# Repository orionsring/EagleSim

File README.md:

# AutoDesk EagleSim
This circuit is a completed senior design project with no patent.
This circuit is to build an Electronic Power Meter. Used to measure power consumpion on electronic devices. Practically a DYI. Do It Yourself! More files with written assembly instructions to come.

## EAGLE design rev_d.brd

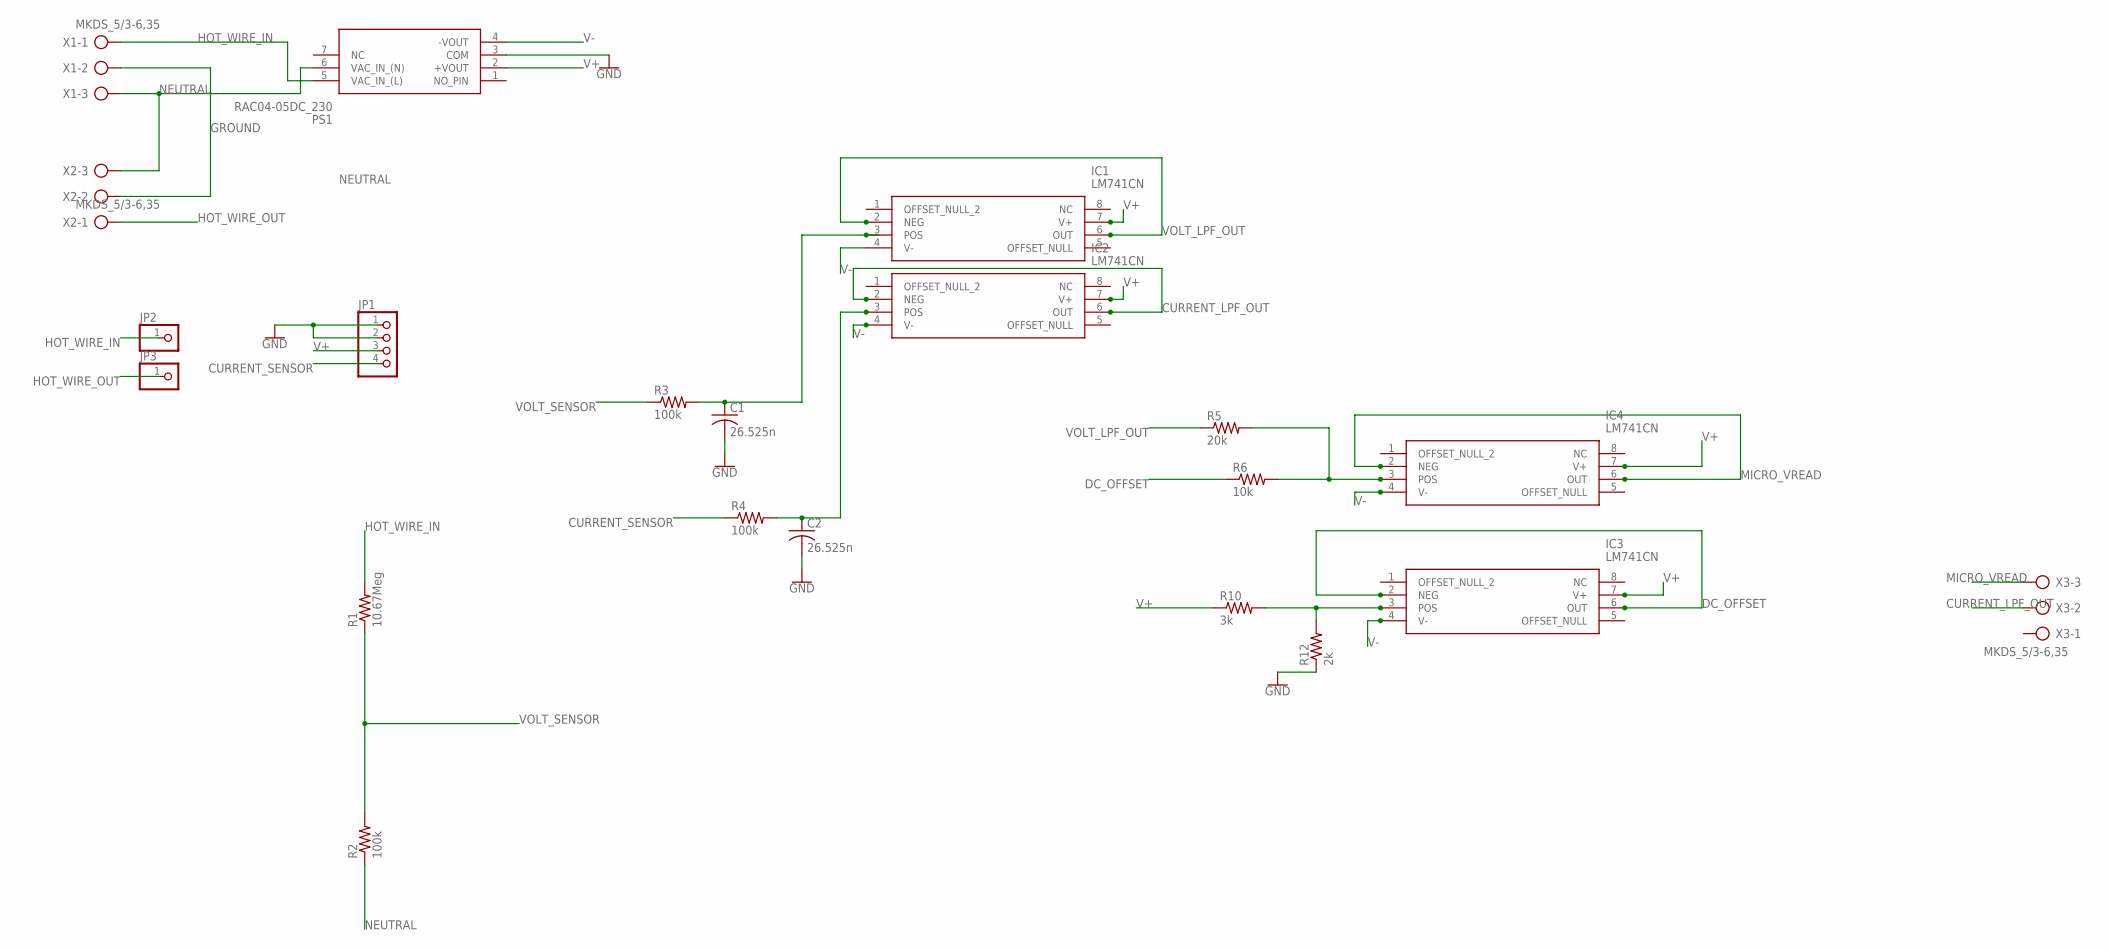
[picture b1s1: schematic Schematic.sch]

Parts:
C1, C2: 26.525n; C025-040X050; MPN MC0805B224K500A5.08MM
IC1, IC2, IC3, IC4: LM741CN; DIP254P762X508-8
JP1: PINHD-1X4; 1X04
JP2, JP3: PINHD-1X1; 1X01
PS1: RAC04-05DC_230; RAC04-0512DC230
R1: 10.67Meg; 0617/22
R2: 100k; 0617/22; MPN MFR3-100KFC
R3, R4: 100k; 0617/22; MPN MFR3-1K0FC
R5: 20k; 0617/22; MPN MFR4-20KFI
R6: 10k; 0617/22; MPN CCF5510K0FKE36
R10: 3k; 0617/22; MPN MFR4 3K3 1%
R12: 2k; 0617/22; MPN MFR4-2K0FI
X1, X2, X3: MKDS_5/3-6,35; MKDS_5/3-635

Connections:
CURRENT_LPF_OUT: IC2.2 (NEG), IC2.6 (OUT), X3.2
CURRENT_SENSOR: JP1.4, R4.1
DC_OFFSET: IC3.2 (NEG), IC3.6 (OUT), R6.1
GND: C1.2, C2.2, JP1.1, JP1.2, PS1.3 (COM), R12.1
GROUND: X1.2, X2.2
HOT_WIRE_IN: JP2.1, PS1.5 (VAC_IN_(L)), R1.2, X1.1
HOT_WIRE_OUT: JP3.1, X2.1
MICRO_VREAD: IC4.2 (NEG), IC4.6 (OUT), X3.3
unnamed: C1.1, IC1.3 (POS), R3.2
unnamed: C2.1, IC2.3 (POS), R4.2
unnamed: IC4.3 (POS), R5.2, R6.2
unnamed: IC3.3 (POS), R10.2, R12.2
NEUTRAL: PS1.6 (VAC_IN_(N)), R2.1, X1.3, X2.3
V+: IC1.7 (V+), IC2.7 (V+), IC3.7 (V+), IC4.7 (V+), JP1.3, PS1.2 (+VOUT), R10.1
V-: IC1.4 (V-), IC2.4 (V-), IC3.4 (V-), IC4.4 (V-), PS1.4 (-VOUT)
VOLT_LPF_OUT: IC1.2 (NEG), IC1.6 (OUT), R5.1
VOLT_SENSOR: R1.1, R2.2, R3.1

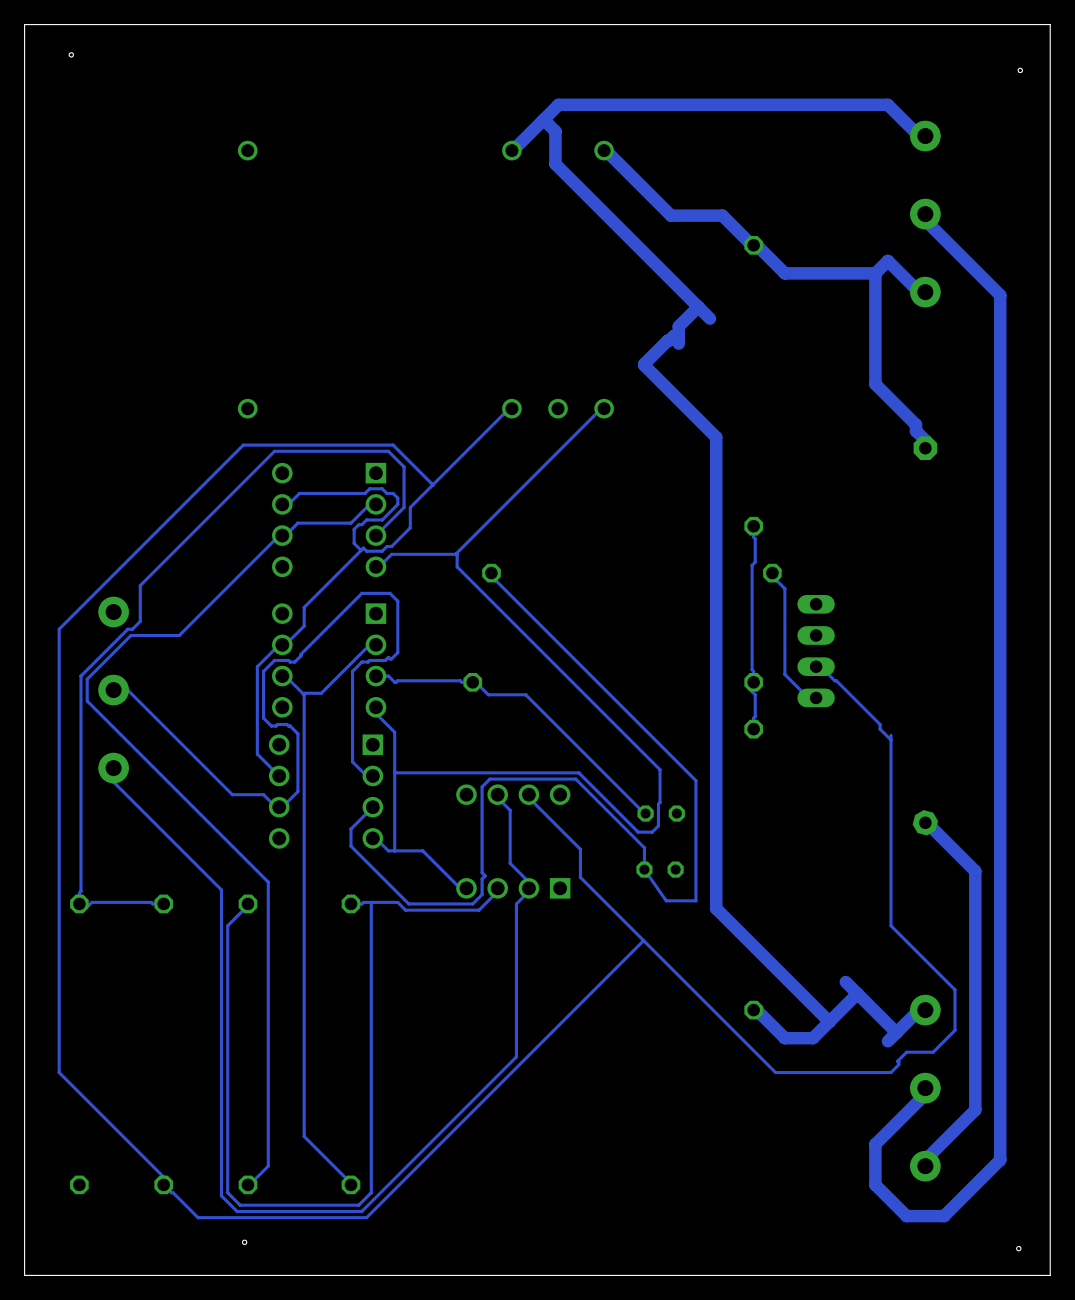
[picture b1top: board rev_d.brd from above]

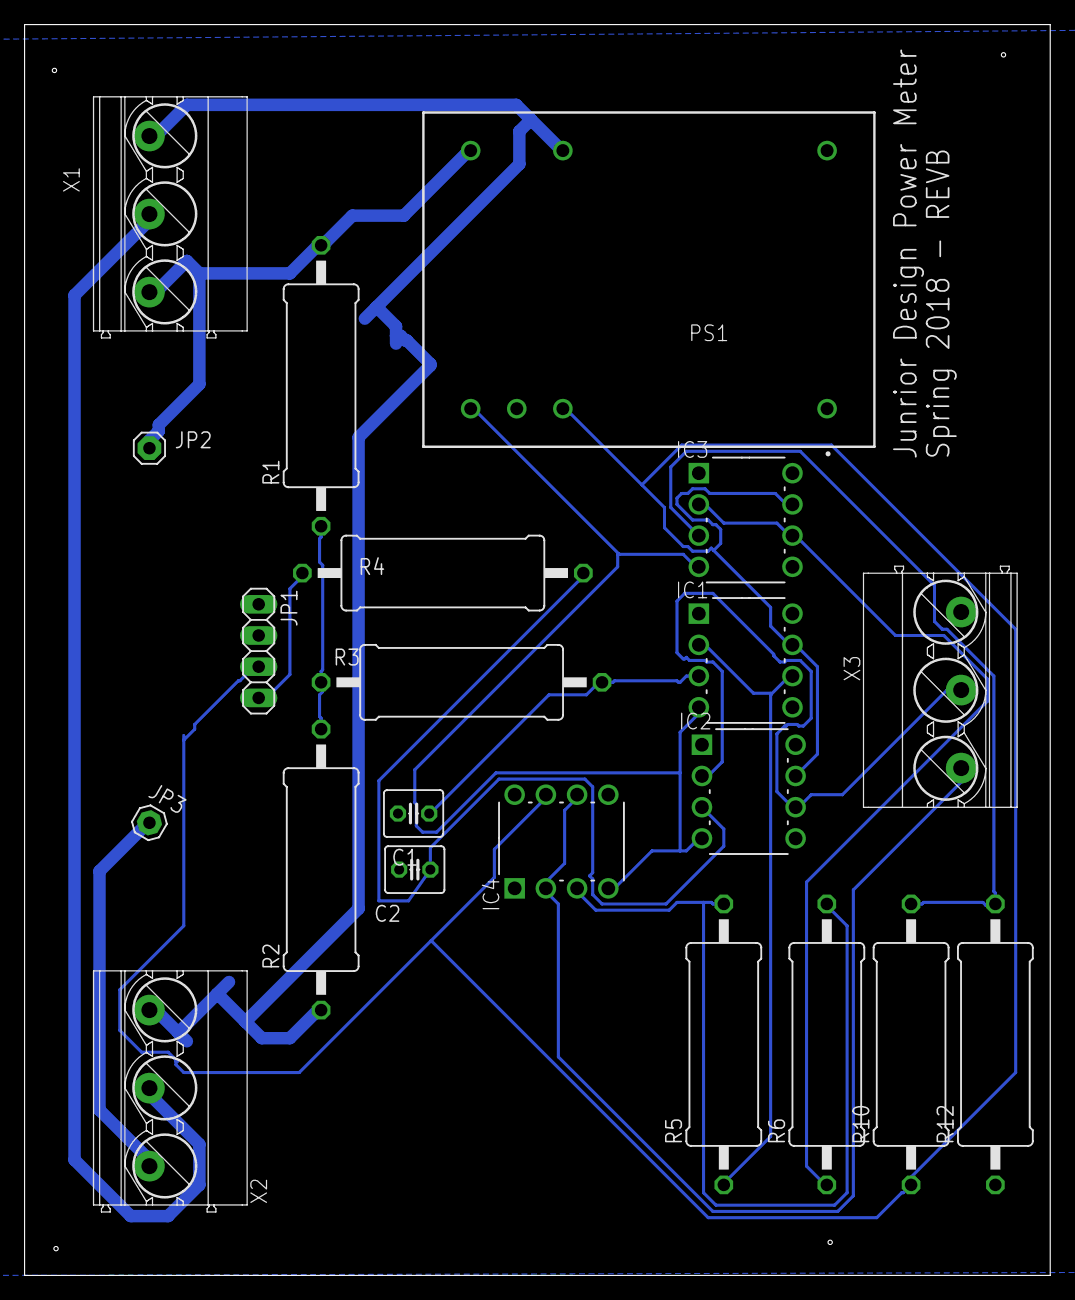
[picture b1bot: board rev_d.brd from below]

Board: 2 copper layers, 83.5 x 101.8 mm, 21 parts (21 on the bottom side), 17 nets.

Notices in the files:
parts and their libraries:
SparkFun-PowerSymbols: Licensing: Creative Commons ShareAlike 4.0 International - https://creativecommons.org/licenses/by-sa/4.0
